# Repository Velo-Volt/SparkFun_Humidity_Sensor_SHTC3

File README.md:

SparkFun Humidity Sensor - SHTC3 (Qwiic)
========================================

[*SparkFun Humidity Sensor - SHTC3 (Qwiic)*](https://www.sparkfun.com/products/16467)

The SparkFun Humidity Sensor - SHTC3 (Qwiic) is an I<sup>2</sup>C enabled humidity and temperature sensor.

Repository Contents
-------------------

* **/Documentation** - Data sheets, additional product information
* **/Hardware** - Eagle design files (.brd, .sch)
* **/Production** - Production panel files (.brd)

Documentation
--------------
* **[SHTC3 Arduino Library](https://github.com/sparkfun/SparkFun_SHTC3_Arduino_Library)** - Arduino library for the SHTC3.
* **[Hookup Guide](https://learn.sparkfun.com/tutorials/sparkfun-humidity-sensor-breakout---shtc3-qwiic-hookup-guide)** - Basic hookup guide for the Humidity Sensor - SHTC3 (Qwiic).
* **[SparkFun Fritzing repo](https://github.com/sparkfun/Fritzing_Parts)** - Fritzing diagrams for SparkFun products.
* **[SparkFun 3D Model repo](https://github.com/sparkfun/3D_Models)** - 3D models of SparkFun products. 

Product Versions
----------------
* [SPX-15074](https://www.sparkfun.com/products/15074)- Original SparkX version of the Humidity Sensor - SHTC3 (Qwiic).

License Information
-------------------

This product is _**open source**_! 

Please review the LICENSE.md file for license information. 

If you have any questions or concerns on licensing, please contact techsupport@sparkfun.com.

Distributed as-is; no warranty is given.

- Your friends at SparkFun.

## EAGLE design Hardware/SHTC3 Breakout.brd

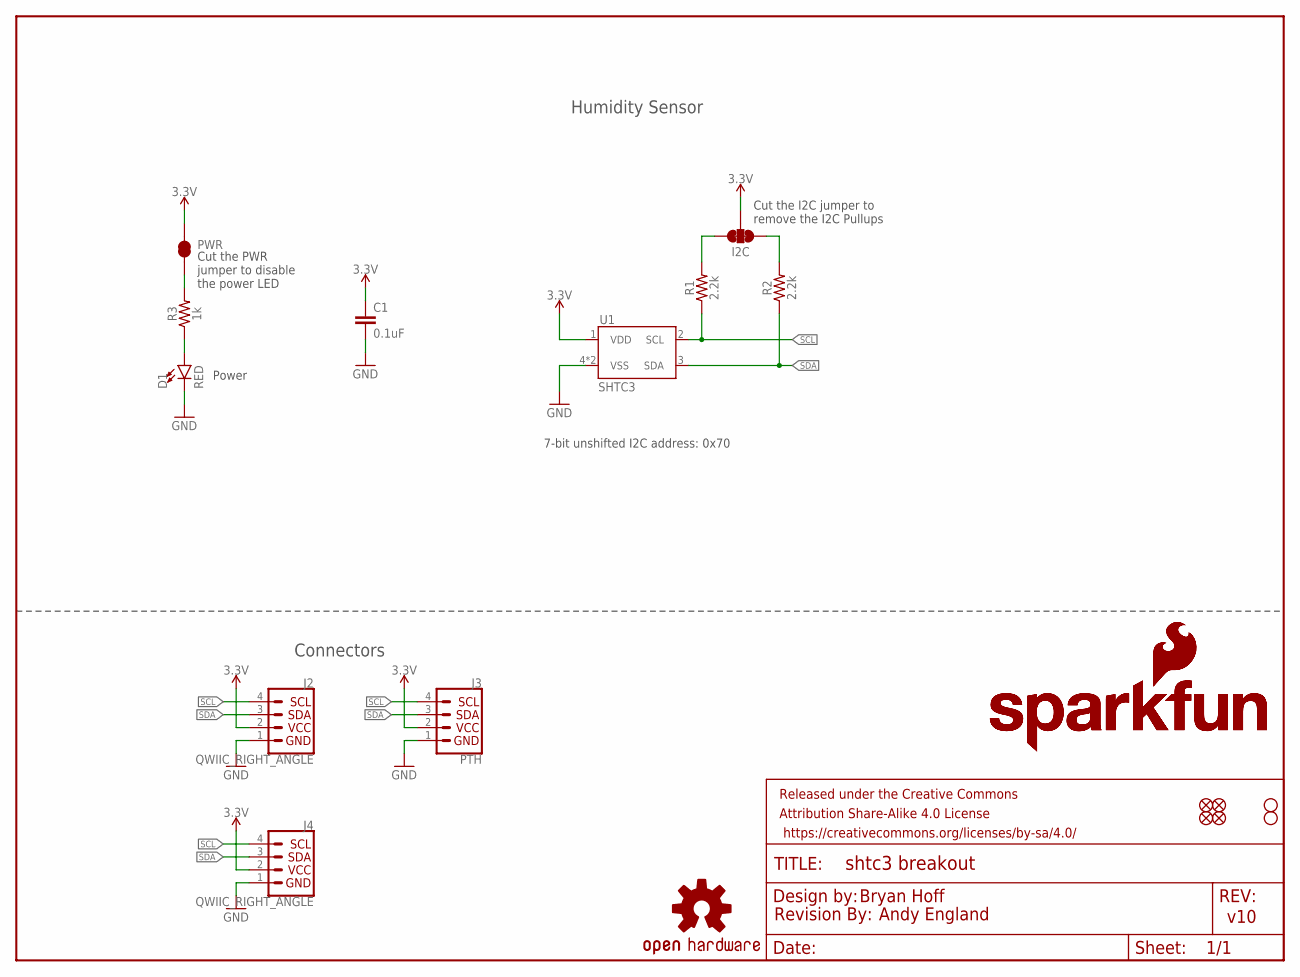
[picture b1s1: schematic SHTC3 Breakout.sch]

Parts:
C1: 0.1uF; 0603
D1: RED; LED-0603
FRAME1: FRAME-LETTER; CREATIVE_COMMONS
I2C: JUMPER-SMT_3_2-NC_TRACE_SILK; SMT-JUMPER_3_2-NC_TRACE_SILK
J2, J4: QWIIC_RIGHT_ANGLE; JST04_1MM_RA
J3: PTH; 1X04_NO_SILK
JP1, JP2, JP5, JP6: FIDUCIALUFIDUCIAL; MICRO-FIDUCIAL
JP3, JP4: STAND-OFF
LOGO1: OSHW-LOGOMINI; OSHW-LOGO-MINI
LOGO2, LOGO3: SFE_LOGO_NAME_FLAME.1_INCH; SFE_LOGO_NAME_FLAME_.1
LOGO4: REVISION
PWR: JUMPER-SMT_2_NC_TRACE_NO-SILK; SMT-JUMPER_2_NC_TRACE_NO-SILK
R1, R2: 2.2k; 0603
R3: 1k; 0603
U1: SHTC3

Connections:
3.3V: C1.1, I2C.2, J2.2, J3.2 (VCC), J4.2, PWR.2, U1.1 (VDD)
GND: C1.2, D1.C, J2.1, J3.1 (GND), J4.1, U1.4 (VSS), U1.5 (VSS)
unnamed: I2C.3, R1.2
unnamed: I2C.1, R2.2
unnamed: D1.A, R3.1
unnamed: PWR.1, R3.2
SCL: J2.4, J3.4 (SCL), J4.4, R1.1, U1.2 (SCL)
SDA: J2.3, J3.3 (SDA), J4.3, R2.1, U1.3 (SDA)

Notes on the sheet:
Bryan Hoff
v10
7-bit unshifted I2C address: 0x70
Power
Connectors
Cut the I2C jumper to remove the I2C Pullups
Humidity Sensor
Cut the PWR jumper to disable the power LED
Andy England

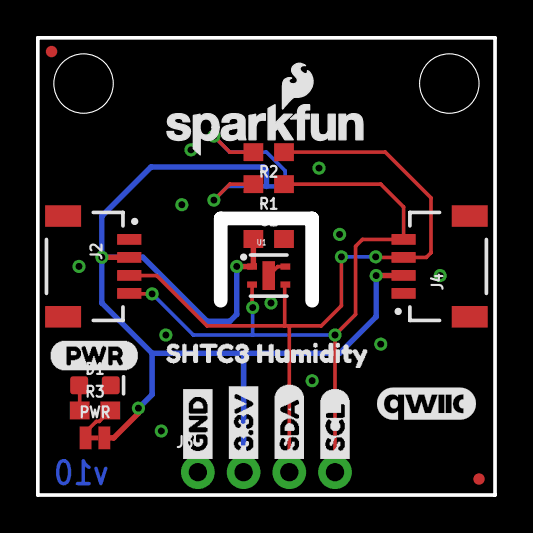
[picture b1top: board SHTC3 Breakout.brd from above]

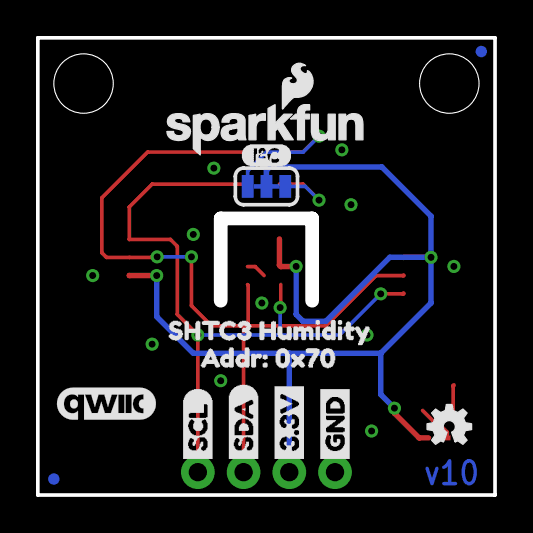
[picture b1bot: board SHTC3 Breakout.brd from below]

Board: 2 copper layers, 24.8 x 24.8 mm, 37 parts (13 on the bottom side), 8 nets.

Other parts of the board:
U$1: ADDR#_0X700
U$3, U$22: GND1
U$4, U$21: 3#3V2
U$5, U$27: SDA8
U$6, U$26: SCL9
U$7, U$8: SHTC3_HUMIDITY1
U$9: I_SUPER2_C-()-03
U$10: (PWR)
U$11, U$12: QWIIC_5.5MM

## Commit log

2020-03-30 pre review commit
2020-03-31 post review/checklist changes, ready for QC double check
2020-03-31 adding in production files
2020-04-13 Updating README
    Updating Readme file.
2020-04-28 Updating README
    Adding new photo.
2020-05-07 Deleting Test Sketch
    Test sketch is not needed as we have the Arduino Library. Removing.
2020-05-08 Update README.md
    link product version

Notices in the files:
parts and their libraries:
SparkFun-Resistors: Licensing: Creative Commons ShareAlike 4.0 International - https://creativecommons.org/licenses/by-sa/4.0
SparkFun-Aesthetics: Released under the Creative Commons Attribution Share-Alike 4.0 License
SparkFun-Aesthetics: https://creativecommons.org/licenses/by-sa/4.0
